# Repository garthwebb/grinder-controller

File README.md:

# grinder-controller

A motor controller for the coffee grinder project.  It makes use of the tachometer wires from the motor to detect when the motor is grinding coffee beans vs when its free running.  A three position toggle switch (on-momentary, off, on-momentary) is used to control the grinder; toggling and releasing in one direction will start automatic grinding, where the motor will only turn off when it detects no more coffee is present.  Toggling in the other direction will grind until the toggle is released, then stop.

This projet includes the following files and directories:

* Coffee Grinder.pdf - A state diagram describing the new controller
* README.md - This file
* pcb-layout - Eagle files for the PCB designed and created to control the motor.
* src - AVR C code that runs the controller functionality

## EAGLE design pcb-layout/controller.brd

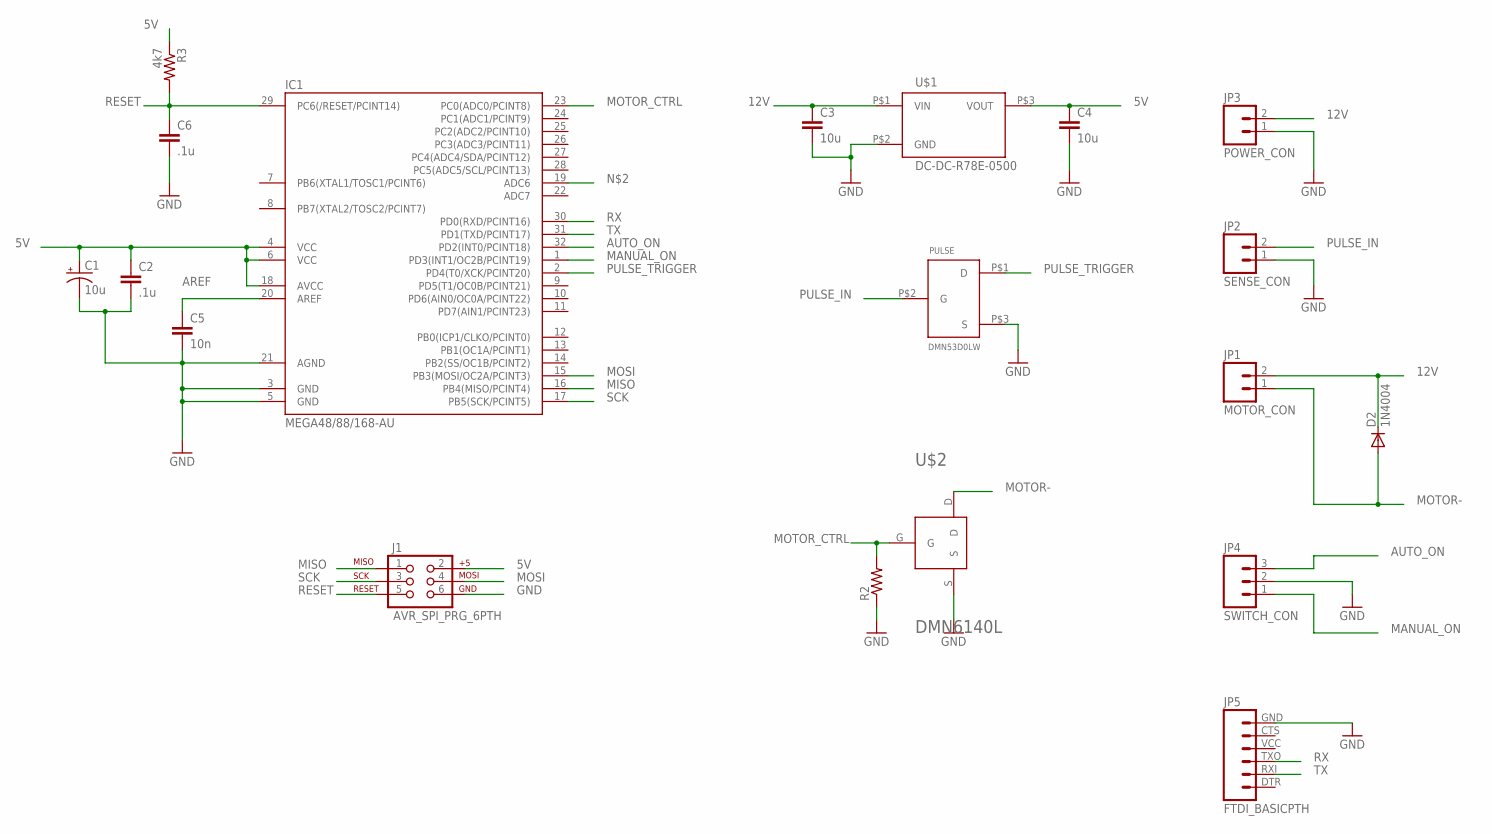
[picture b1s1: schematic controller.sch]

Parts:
C1: 10u; EIA3216
C2, C6: .1u; 0805
C3, C4: 10u; 0805
C5: 10n; 0805
D2: 1N4004; DO41-10
IC1: MEGA48/88/168-AU; TQFP32-08
J1: AVR_SPI_PRG_6PTH; 2X3
JP1: MOTOR_CON; 1X02_LONGPADS
JP2: SENSE_CON; 1X02_LONGPADS
JP3: POWER_CON; 1X02_LONGPADS
JP4: SWITCH_CON; 1X03_NO_SILK
JP5: FTDI_BASICPTH; FTDI_BASIC
PULSE: DMN53D0LW; SOT-323
R2: RESISTOR1206; 1206
R3: 4k7; 1206
U$1: DC-DC-R78E-0500
U$2: DMN6140L; SOT-32-DIODES

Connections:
5V: C1.A (+), C2.1, C4.1, IC1.4 (VCC), IC1.6 (VCC), IC1.18 (AVCC), J1.2, R3.1, U$1.P$3 (VOUT)
12V: C3.1, D2.C, JP1.2, JP3.2, U$1.P$1 (VIN)
AREF: C5.1, IC1.20 (AREF)
AUTO_ON: IC1.32 (PD2(INT0/PCINT18)), JP4.3
GND: C1.C (-), C2.2, C3.2, C4.2, C5.2, C6.2, IC1.3 (GND), IC1.5 (GND), IC1.21 (AGND), J1.6, JP2.1, JP3.1, JP4.2, JP5.GND (6), PULSE.P$3 (S), R2.1, U$1.P$2 (GND), U$2.S
MANUAL_ON: IC1.1 (PD3(INT1/OC2B/PCINT19)), JP4.1
MISO: IC1.16 (PB4(MISO/PCINT4)), J1.1
MOSI: IC1.15 (PB3(MOSI/OC2A/PCINT3)), J1.4
MOTOR-: D2.A, JP1.1, U$2.D
MOTOR_CTRL: IC1.23 (PC0(ADC0/PCINT8)), R2.2, U$2.G
PULSE_IN: JP2.2, PULSE.P$2 (G)
PULSE_TRIGGER: IC1.2 (PD4(T0/XCK/PCINT20)), PULSE.P$1 (D)
RESET: C6.1, IC1.29 (PC6(/RESET/PCINT14)), J1.5, R3.2
RX: IC1.30 (PD0(RXD/PCINT16)), JP5.TXO (3)
SCK: IC1.17 (PB5(SCK/PCINT5)), J1.3
TX: IC1.31 (PD1(TXD/PCINT17)), JP5.RXI (2)

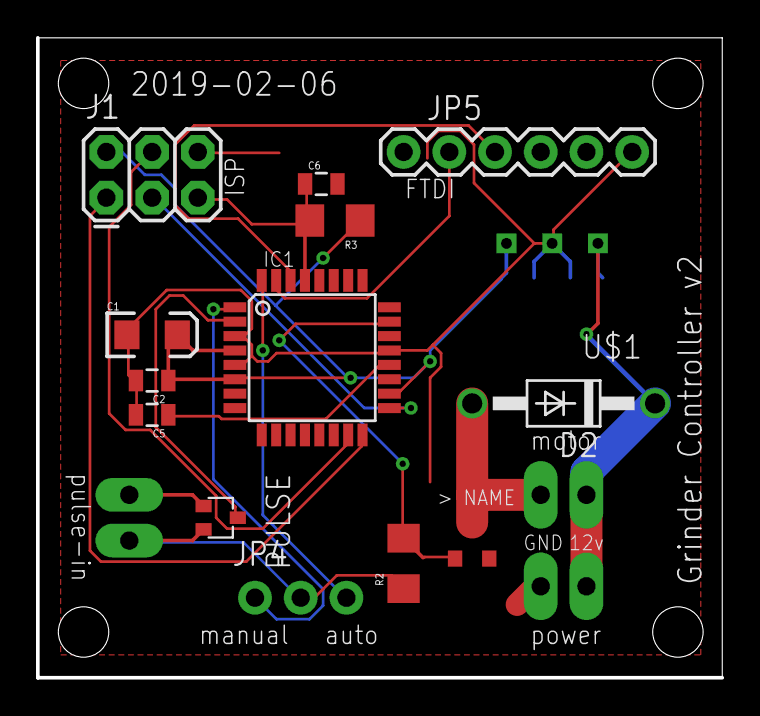
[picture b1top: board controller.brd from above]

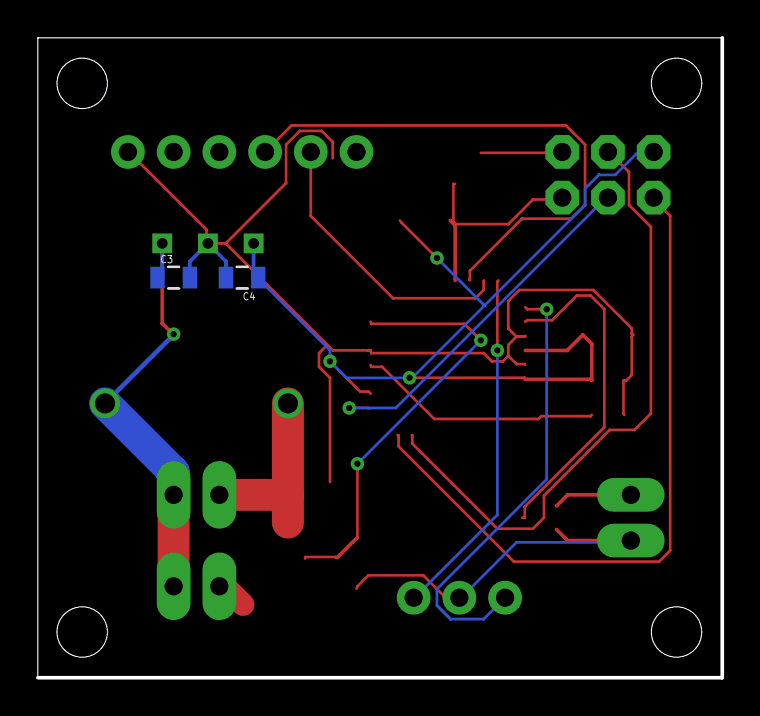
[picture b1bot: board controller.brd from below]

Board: 2 copper layers, 38.0 x 35.5 mm, 19 parts (2 on the bottom side), 16 nets.

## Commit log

2018-02-26 New files from project
2018-02-26 Remove uneeded LED blinking code
2018-02-27 Speed detection and switch monitoring (test) working
2018-03-01 Split functionality into different source files.
    Added a state machine to handle grinder functions
2018-03-03 Clarified some comments, added a stop_motor call
    The stop_motor() call was needed to make sure in the manual_run_clearing state, that nothing is running.
2018-03-03 State diagram representing state_machine.c
2018-03-05 Moved code files into a new src directory
2018-03-05 Got rid of symlink in preparation for real directory
2018-03-05 Add the eagle files for the controller
2018-03-05 Updated readme with meaningful info
2019-02-07 Updated board to fix a number of problems
    * Used DMN53D0LW layout for the DMN6140L part which has a smaller footprint. Created a new layout for DMN6140L and used that
    * Removed resistor in series with flyback diode.
    * Updated diode layout to be 1N4004 compatible
    * Removed diode across FET (was there assuming it would be a BJT)
    * Fixed reset resistor, attaching it to VCC rather than GND
    * Added a cap from reset to ground

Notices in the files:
parts and their libraries:
SparkFun-Connectors: Licensing: CC v3.0 Share-Alike You are welcome to use this library for commercial purposes.
